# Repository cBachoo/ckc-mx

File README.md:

# ckc-mx
A drop in pcb for sanwa buttons to use MX compatible switches.

Note:
This is a untested design, this is also one of my first ever PCB projects so I'm not even sure the schematic itself is correct.

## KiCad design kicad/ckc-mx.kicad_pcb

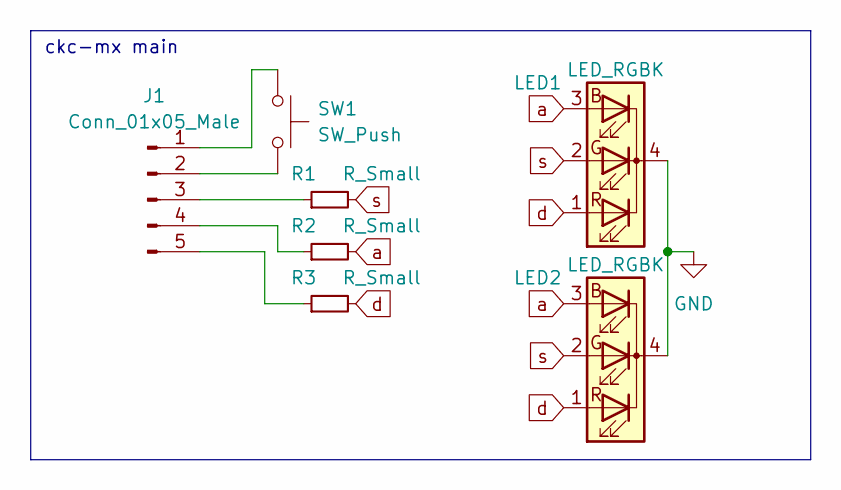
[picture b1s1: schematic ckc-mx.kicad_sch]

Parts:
J1: Conn_01x05_Male; JST_PH_B5B-PH-K_1x05_P2.00mm_Vertical
LED1, LED2: LED_RGBK; LED_D5.0mm-4_RGB_Wide_Pins
R1, R2, R3: R_Small; R_0805_2012Metric_Pad1.20x1.40mm_HandSolder
SW1: SW_Push; MX100

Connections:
GND: LED1.4 (K), LED2.4 (K)
unnamed: J1.1, SW1.1
unnamed: J1.2, SW1.2
unnamed: J1.3, R1.1
unnamed: J1.4, R2.1
unnamed: J1.5, R3.1
a: LED1.3 (BA), LED2.3 (BA), R2.2
d: LED1.1 (RA), LED2.1 (RA), R3.2
s: LED1.2 (GA), LED2.2 (GA), R1.2

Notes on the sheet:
ckc-mx main

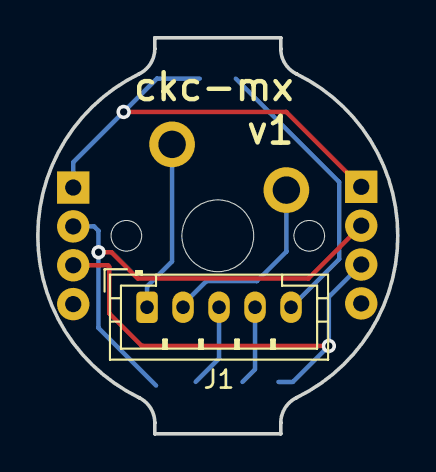
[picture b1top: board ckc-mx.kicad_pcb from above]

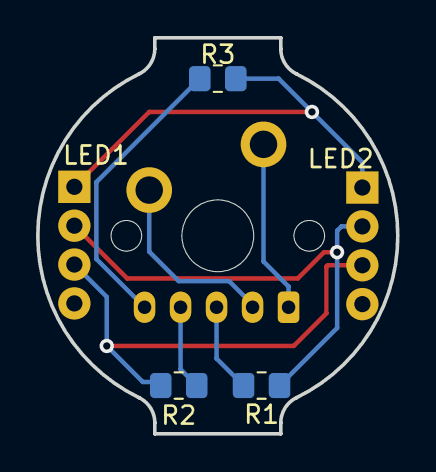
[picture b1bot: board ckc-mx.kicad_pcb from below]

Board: 2 copper layers, 20.0 x 22.0 mm, 7 parts (5 on the bottom side), 9 nets.

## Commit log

2023-06-19 test
2023-06-19 added libraries
2023-06-19 drc is cool
2023-06-19 updated project
